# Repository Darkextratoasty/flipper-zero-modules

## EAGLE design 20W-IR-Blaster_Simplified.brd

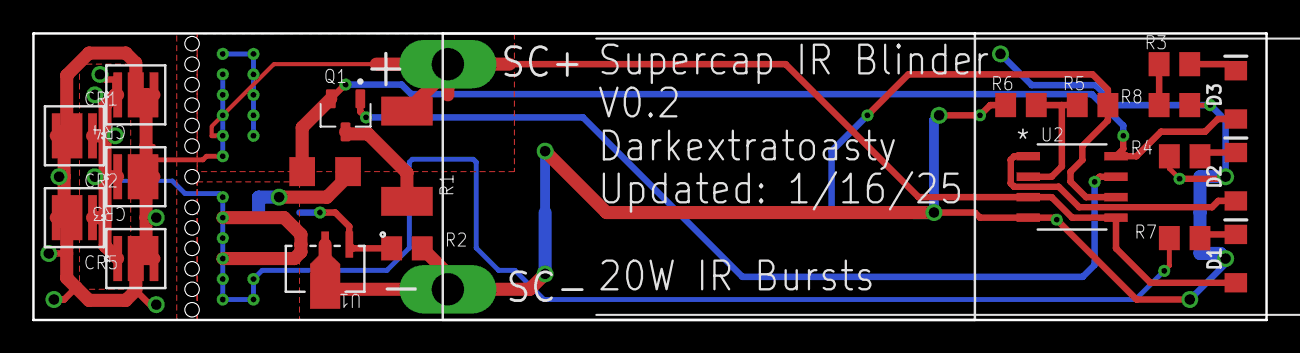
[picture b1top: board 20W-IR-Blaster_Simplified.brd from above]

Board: 2 copper layers, 76.5 x 17.8 mm, 23 parts (0 on the bottom side), 15 nets.

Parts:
CR1, CR2, CR3, CR4, CR5: VSMA1094250; DIODE_VSMA1094250_VIS
D1: Blue; LED-1206
D2: Green; LED-1206
D3: Amber; LED-1206
F1: FUSE; R1206
Q1: AO3401
R1: 5R; R2512
R2, R3, R4, R5, R7: 2K7; R0805
R6: 27K; R0805
R8: 1K; R0805
SC+: PTR1PAD1-20Y; P1-20Y
SC-: PTR1PAD1-20Y; P1-20Y
U1: BSS87; SOT89_NXP
U2: LM393DT; SO8_STM
U$1: BOTH-SMD

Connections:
5VIN: F1.1, U$1.19
+3V3: R5.2, U2.6, U$1.1
GND: R2.1, R4.2, R6.1, R8.1, SC-.TP, U1.1, U2.4, U$1.3, U$1.10, U$1.25
INPUT: R2.2, U1.3, U$1.26
unnamed: Q1.3, R1.1
unnamed: CR1.2, CR1.3, CR2.2, CR2.3, CR3.2, CR3.3, CR4.2, CR4.3, CR5.2, CR5.3, D1.A, R1.2, SC+.TP, U2.3, U2.5
unnamed: D2.A, U2.1
unnamed: R5.1, R6.2, U2.2
unnamed: Q1.1, U2.7
unnamed: D2.C, R4.1
unnamed: D1.C, R7.2
unnamed: D3.C, R3.2
unnamed: R3.1, R8.2
unnamed: D3.A, F1.2, Q1.2, U2.8
unnamed: CR1.1, CR2.1, CR3.1, CR4.1, CR5.1, R7.1, U1.2

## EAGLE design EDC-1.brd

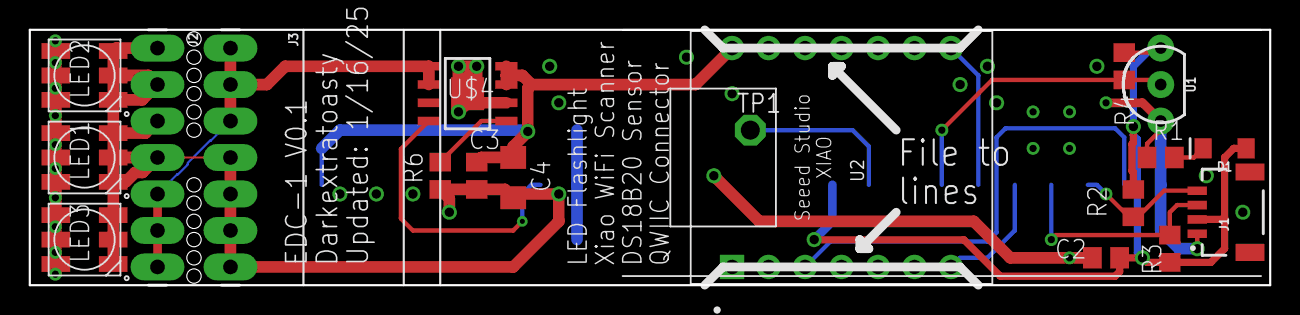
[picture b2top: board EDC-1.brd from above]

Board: 2 copper layers, 86.4 x 17.8 mm, 20 parts (0 on the bottom side), 14 nets.

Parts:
C2, C3: 1uf; C0805
C4: 22uf; C3216
D1: Yellow; LED-1206
J1: QWIIC_RIGHT_ANGLE; JST04_1MM_RA
J2, J3: 1X07_LONGPADS
LED1, LED2, LED3: RGBLED5050
R1: 2K2; R0805
R2, R3, R4, R6: 10K; R0805
TP1: PTR1PAD1-13; P1-13
U1: DS18B20; TO-92-AMMO
U2: XIAO-THRUHOLE; XIAO-GENERIC-THRUHOLE-MODULE14P-2.54-21X17.8MM
U$1: BOTH-SMD
U$4: CN5711; SOIC127P600X175-9N

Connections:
+3V3: C2.1, D1.A, J1.2, R2.1, R3.1, R4.1, U1.3, U$1.1
+5V: C3.1, C4.1, U2.14, U$1.19, U$4.3, U$4.4
FLIP_RX: U2.7, U$1.6
FLIP_TX: U2.8, U$1.5
GND: C2.2, C3.2, C4.2, J1.1, J2.1, J2.2, J2.3, J2.4, J3.4, J3.5, J3.6, J3.7, LED1.4, LED1.5, LED1.6, LED2.4, LED2.5, LED2.6, LED3.4, LED3.5, LED3.6, R1.1, R6.1, U1.1, U2.13, U$1.3, U$1.10, U$1.25, U$4.2, U$4.9
LED+: J2.5, J2.6, J2.7, J3.1, J3.2, J3.3, LED1.1, LED1.2, LED1.3, LED2.1, LED2.2, LED2.3, LED3.1, LED3.2, LED3.3, U$4.5, U$4.6
LED_TRIG: U$1.24, U$4.8
unnamed: TP1.TP, U$1.2
unnamed: R6.2, U$4.1
unnamed: D1.C, R1.2
SCL: J1.4, R2.2, U$1.8
SDA: J1.3, R3.2, U$1.7
THERM: R4.2, U1.2, U$1.4
WIFI_CHECK: U2.3, U$1.9

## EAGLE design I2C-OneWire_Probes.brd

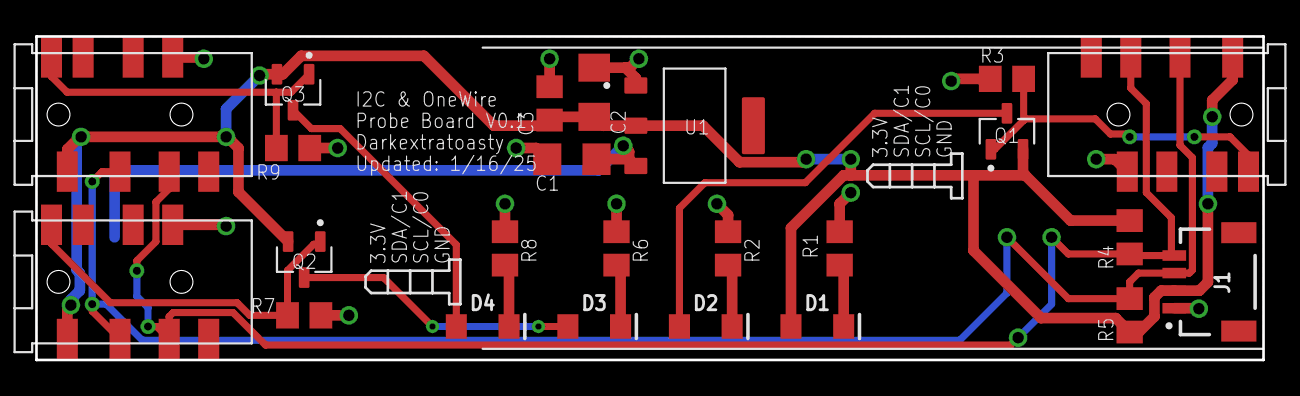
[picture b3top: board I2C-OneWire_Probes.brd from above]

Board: 2 copper layers, 69.8 x 18.4 mm, 25 parts (0 on the bottom side), 15 nets.

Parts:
C1, C2: 22uf; C3216
C3: 100nf; C0805
D1: Red; LED-1206
D2, D3, D4: Blue; LED-1206
J1: QWIIC_RIGHT_ANGLE; JST04_1MM_RA
Q1, Q2, Q3: AO3401
R1, R2, R6, R8: 2k2; R0805
R3, R4, R5, R7, R9: 10k; R0805
U1: AMS1117-3.3; SOT229P700X180-4N
U$1: BOTH-SMD
U$2, U$3, U$4: PJ-3938PJ

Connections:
+3V3: C2.1, C3.1, D1.A, J1.2, Q1.2, Q2.2, Q3.2, R4.2, R5.2, U1.2, U$2.P$1, U$3.P$1, U$4.P$1
+5V: C1.1, U1.3, U$1.19
GND: C1.2, C2.2, C3.2, J1.1, R1.2, R2.1, R3.1, R6.1, R7.1, R8.1, R9.1, U1.1, U$1.3, U$1.10, U$1.25, U$2.P$5, U$3.P$5, U$4.P$5
unnamed: D2.A, Q1.3
unnamed: D2.C, R2.2
unnamed: Q1.1, R3.2, U$2.P$8
unnamed: D3.C, R6.2
unnamed: Q2.1, R7.2, U$3.P$8
unnamed: D4.C, R8.2
unnamed: Q3.1, R9.2, U$4.P$8
unnamed: D1.C, R1.1
unnamed: D3.A, Q2.3
unnamed: D4.A, Q3.3
SCL: J1.4, R4.1, U$1.8, U$2.P$3, U$3.P$3, U$4.P$3
SDA: J1.3, R5.1, U$1.7, U$2.P$2, U$3.P$2, U$4.P$2

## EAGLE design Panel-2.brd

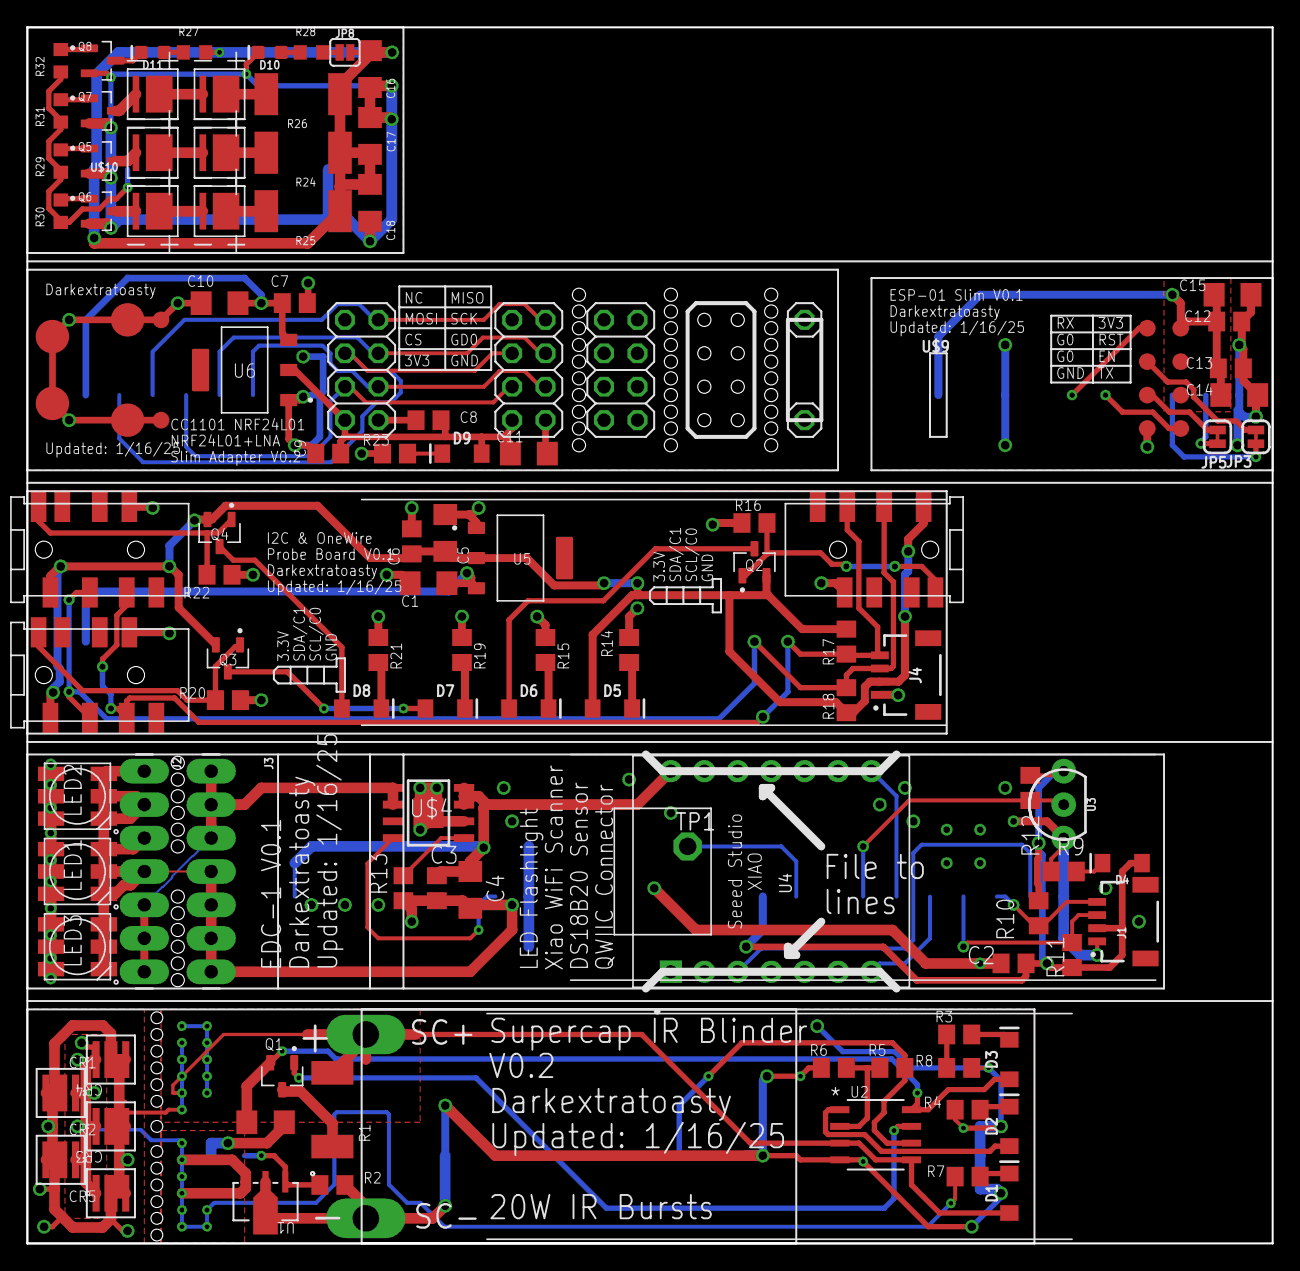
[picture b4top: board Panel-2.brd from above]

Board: 2 copper layers, 94.6 x 92.4 mm, 129 parts (0 on the bottom side), 81 nets.

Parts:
C1, C4, C5, C10, C11, C14, C15: 22uf; C3216
C2, C3, C9, C13: 1uf; C0805
C6, C7, C8, C12: 100nf; C0805
C16, C17, C18: 22uF; C3216
CR1, CR2, CR3, CR4, CR5: VSMA1094250; DIODE_VSMA1094250_VIS
D1, D6, D7, D8: Blue; LED-1206
D2: Green; LED-1206
D3: Amber; LED-1206
D4: Yellow; LED-1206
D5, D9: Red; LED-1206
D10: Orange; LED-0603
D11: Blue; LED-0603
F1: FUSE; R1206
J1, J4: QWIIC_RIGHT_ANGLE; JST04_1MM_RA
J2, J3: 1X07_LONGPADS
JP1, JP2, JP4: 2X04
JP3, JP5: JUMPER-SMT_2_NC_TRACE_SILK; SMT-JUMPER_2_NC_TRACE_SILK
JP6, JP7: 1X01
JP8: JUMPER-SMT_2_NC_PASTE_SILK; SMT-JUMPER_2_NC_PASTE_SILK
LED1, LED2, LED3: RGBLED5050
Q1, Q2, Q3, Q4: AO3401
Q5, Q6, Q7, Q8: MMBT2222A; SOT95P240X120-3N
R1: 5R; R2512
R2, R3, R4, R5, R7: 2K7; R0805
R6: 27K; R0805
R8: 1K; R0805
R9, R23: 2K2; R0805
R10, R11, R12, R13: 10K; R0805
R14, R15, R19, R21: 2k2; R0805
R16, R17, R18, R20, R22: 10k; R0805
R24, R25, R26: 5R1; R2512
R27, R28: 2K2; R0603
R29, R30, R31, R32: 1K; R0603
SC+: PTR1PAD1-20Y; P1-20Y
SC-: PTR1PAD1-20Y; P1-20Y
TP1: PTR1PAD1-13; P1-13
TP2, TP3, TP8, TP9, TP10, TP11, TP12, TP13, TP14, TP15: PTR1B1,27; B1,27
TP4, TP5, TP6, TP7: PTR1B2,54; B2,54
U1: BSS87; SOT89_NXP
U2: LM393DT; SO8_STM
U3: DS18B20; TO-92-AMMO
U4: XIAO-THRUHOLE; XIAO-GENERIC-THRUHOLE-MODULE14P-2.54-21X17.8MM
U5, U6: AMS1117-3.3; SOT229P700X180-4N
U$1, U$2, U$3: BOTH-SMD
U$4: CN5711; SOIC127P600X175-9N
U$5, U$6, U$7: PJ-3938PJ
U$8, U$10: LEFT-H1-SMD
U$9: RIGHT-H2-SMD
U$11, U$12, U$13, U$14, U$15, U$16: XSSYSE03-EMC3838A-H90

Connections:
5VIN: F1.1, U$1.19
+3V1: C2.1, D4.A, J1.2, R10.1, R11.1, R12.1, U3.3, U$2.1
+3V2: C5.1, C6.1, D5.A, J4.2, Q2.2, Q3.2, Q4.2, R17.2, R18.2, U5.2, U$5.P$1, U$6.P$1, U$7.P$1
+3V3: R5.2, U2.6, U$1.1
+3V4: C8.1, C9.1, C11.1, D9.A, JP1.2, JP2.2, U6.2
+3V5: C12.1, C13.1, C14.1, C15.1, TP11.TP, U$9.1
+5V: C3.1, C4.1, U4.14, U$2.19, U$4.3, U$4.4
+5V1: C1.1, U5.3, U$3.19
+5V2: C7.1, C10.1, U6.3, U$8.1
+5V3: C16.1, C17.1, C18.1, JP8.2, R24.2, R25.2, R26.2, R27.2, U$10.1
CHA: JP3.2, TP14.TP
CHB: JP5.2, TP13.TP
CS: JP1.4, JP2.4, U$8.4
FLIP_RX: U4.7, U$2.6
FLIP_TX: U4.8, U$2.5
FRX: TP8.TP, U$9.6
FTX: TP15.TP, U$9.5
GD0: JP1.3, JP2.3, U$8.6
GND: R2.1, R4.2, R6.1, R8.1, SC-.TP, U1.1, U2.4, U$1.3, U$1.10, U$1.25
GND1: C2.2, C3.2, C4.2, J1.1, J2.1, J2.2, J2.3, J2.4, J3.4, J3.5, J3.6, J3.7, LED1.4, LED1.5, LED1.6, LED2.4, LED2.5, LED2.6, LED3.4, LED3.5, LED3.6, R9.1, R13.1, U3.1, U4.13, U$2.3, U$2.10, U$2.25, U$4.2, U$4.9
GND2: C1.2, C5.2, C6.2, J4.1, R14.2, R15.1, R16.1, R19.1, R20.1, R21.1, R22.1, U5.1, U$3.3, U$3.10, U$3.25, U$5.P$5, U$6.P$5, U$7.P$5
GND3: C7.2, C8.2, C9.2, C10.2, C11.2, JP1.1, JP2.1, R23.1, TP2.TP, TP3.TP, TP4.TP, TP5.TP, TP6.TP, TP7.TP, U6.1, U$8.8
GND4: C12.2, C13.2, C14.2, C15.2, TP12.TP, U$9.3, U$9.10
GND5: C16.2, C17.2, C18.2, D10.C, Q5.2, Q6.2, Q7.2, Q8.2, U$10.8
INPUT: R2.2, U1.3, U$1.26
LED+: J2.5, J2.6, J2.7, J3.1, J3.2, J3.3, LED1.1, LED1.2, LED1.3, LED2.1, LED2.2, LED2.3, LED3.1, LED3.2, LED3.3, U$4.5, U$4.6
LED_TRIG: U$2.24, U$4.8
MISO: JP1.7, JP2.7, U$8.3
MOSI: JP1.6, JP2.6, U$8.2
unnamed: Q1.3, R1.1
unnamed: CR1.2, CR1.3, CR2.2, CR2.3, CR3.2, CR3.3, CR4.2, CR4.3, CR5.2, CR5.3, D1.A, R1.2, SC+.TP, U2.3, U2.5
unnamed: D2.A, U2.1
unnamed: R5.1, R6.2, U2.2
unnamed: Q1.1, U2.7
unnamed: D2.C, R4.1
unnamed: D1.C, R7.2
unnamed: D3.C, R3.2
unnamed: R3.1, R8.2
unnamed: R13.2, U$4.1
unnamed: D3.A, F1.2, Q1.2, U2.8
unnamed: D4.C, R9.2
unnamed: CR1.1, CR2.1, CR3.1, CR4.1, CR5.1, R7.1, U1.2
unnamed: TP1.TP, U$2.2
unnamed: D6.C, R15.2
unnamed: Q2.1, R16.2, U$5.P$8
unnamed: D7.C, R19.2
unnamed: Q3.1, R20.2, U$6.P$8
unnamed: D8.C, R21.2
unnamed: Q4.1, R22.2, U$7.P$8
unnamed: D5.C, R14.1
unnamed: D6.A, Q2.3
unnamed: D7.A, Q3.3
unnamed: D8.A, Q4.3
unnamed: D9.C, R23.2
unnamed: JP3.1, U$9.8
unnamed: JP5.1, U$9.9
unnamed: D10.A, R28.1
unnamed: Q5.1, R29.2
unnamed: Q5.3, U$11.P$2
unnamed: U$11.P$1, U$12.P$2
unnamed: R24.1, U$12.P$1
unnamed: R25.1, U$13.P$1
unnamed: U$13.P$2, U$14.P$1
unnamed: Q6.3, U$14.P$2
unnamed: Q6.1, R30.2
unnamed: Q7.1, R31.2
unnamed: Q7.3, U$15.P$2
unnamed: U$15.P$1, U$16.P$2
unnamed: R26.1, U$16.P$1
unnamed: D11.A, R27.1
unnamed: D11.C, Q8.3
unnamed: Q8.1, R32.2
unnamed: R29.1, R30.1, R31.1, R32.1, U$10.2
unnamed: JP8.1, R28.2
SCK: JP1.5, JP2.5, U$8.5
SCL: J1.4, R10.2, U$2.8
SCL1: J4.4, R17.1, U$3.8, U$5.P$3, U$6.P$3, U$7.P$3
SDA: J1.3, R11.2, U$2.7
SDA1: J4.3, R18.1, U$3.7, U$5.P$2, U$6.P$2, U$7.P$2
THERM: R12.2, U3.2, U$2.4
WIFI_CHECK: U4.3, U$2.9

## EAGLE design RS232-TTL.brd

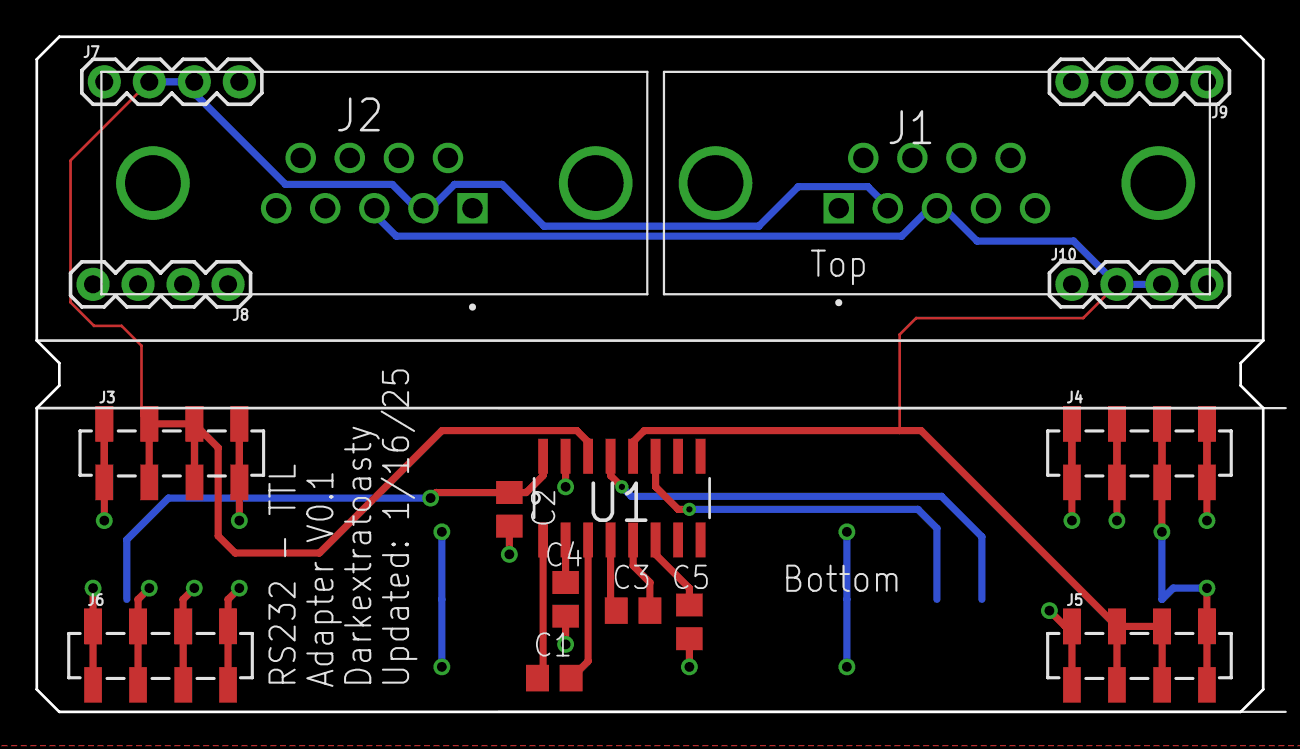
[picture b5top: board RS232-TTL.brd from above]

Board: 2 copper layers, 69.2 x 38.1 mm, 17 parts (0 on the bottom side), 12 nets.

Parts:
C1, C2: 47nf; C0805
C3, C4, C5: 330nf; C0805
J1: L77SDEH09SOL2RM5; AMPHENOL_L77SDEH09SOL2RM5
J2: L717SDEH09POL2RM8; AMPHENOL_L717SDEH09POL2RM8
J3, J4, J5, J6: 1X04_SMD_VERTICAL_COMBO_CENTERED
J7, J8, J9, J10: 1X04
U1: SP3232EEN-L; SOIC127P600X175-16N
U$1: BOTH-SMD

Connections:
+5V: C2.1, U1.16, U$1.19
FLIP_RX: U1.13, U$1.6
FLIP_TX: U1.11, U$1.5
FO_RX: J1.3, J2.3, J5.2, J5.3, J10.2, J10.3, U1.12
FO_TX: J1.2, J2.2, J3.2, J3.3, J7.2, J7.3, U1.14
GND: C2.2, C4.2, C5.1, J1.5, J1.SH1, J1.SH2, J2.5, J2.SH1, J2.SH2, J3.1, J3.4, J4.1, J4.2, J4.3, J4.4, J5.1, J5.4, J6.1, J6.2, J6.3, J6.4, J7.1, J7.4, J8.1, J8.2, J8.3, J8.4, J9.1, J9.2, J9.3, J9.4, J10.1, J10.4, U1.15, U$1.3, U$1.10, U$1.25
unnamed: C4.1, U1.2
unnamed: C1.1, U1.1
unnamed: C3.2, U1.5
unnamed: C3.1, U1.4
unnamed: C1.2, U1.3
unnamed: C5.2, U1.6

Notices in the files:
parts and their libraries:
SparkFun-LED: Licensing: Creative Commons ShareAlike 4.0 International - https://creativecommons.org/licenses/by-sa/4.0
COPYRIGHT: Copyright (C) 2025 Ultra Librarian. All rights reserved.
